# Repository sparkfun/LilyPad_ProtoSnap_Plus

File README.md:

SparkFun LilyPad ProtoSnap Plus
========================================

<table class="table table-hover table-striped table-bordered">
  <tr>
   <td><a href="https://www.sparkfun.com/products/14346"><div align="center"></div></a></center></td>
   <td><a href="https://www.sparkfun.com/products/12922"><div align="center"></div></a></td>
  </tr>
  <tr>
    <td><div align="center">LilyPad ProtoSnap Plus [<a href="https://www.sparkfun.com/products/14346">DEV-14346</a> ]</div></td>
    <td><div align="center">LilyPad ProtoSnap Plus Kit [<a href="https://www.sparkfun.com/products/12922">DEV-12922</a>]</div></td>
  </tr>
</table>

Snappable prototyping board with 32u4, light sensor, buzzer, button, and leds. 

To use the ProtoSnap Plus with Arduino, install the [SparkFun Arduino_Boards](https://github.com/sparkfun/Arduino_Boards) package for avr version 1.1.7 or later.

Base examples for this board are included in the package.  Select "LilyPad USB Plus" as a board type, then see examples for that board.

For extra information on Linux use, see [/Documentation/LinuxInstallation.md](https://github.com/sparkfun/LilyPad_ProtoSnap_Plus/tree/master/Documentation/LinuxInstallation.md).

Repository Contents
-------------------

* **/Documentation** - pin mapping and design information, linux installation info.
* **/Hardware** - Eagle design files (.brd, .sch)
* **/Production** - Production panel files (.brd)

Documentation
--------------
* **[Hookup Guide](https://learn.sparkfun.com/tutorials/lilypad-protosnap-plus-hookup-guide)** - Basic hookup guide for the LilyPad ProtoSnap Plus.
* **[Activity Guide](https://learn.sparkfun.com/tutorials/lilypad-protosnap-plus-activity-guide)** - This guide will get you started with some introductory programming activities exploring each of the LilyPad pieces on the LilyPad ProtoSnap Plus. If you’ve never used Arduino to program before, this guide will walk you through the basics with example code to upload and explore.

Product Versions
----------------
* [DEV-14346](https://www.sparkfun.com/products/14346) - LilyPad ProtoSnap Plus
* [DEV-12922](https://www.sparkfun.com/products/12922) - LilyPad ProtoSnap Plus Kit Version
* [LAB-14529](https://www.sparkfun.com/products/14529) - LilyPad ProtoSnap Plus Lab Pack Version

Version History
---------------
* [V_1.0](https://github.com/sparkfun/LilyPad_ProtoSnap_Plus/tree/V_0.1) - Production release.

License Information
-------------------

This product is _**open source**_! 

Please review the LICENSE.md file for license information. 

If you have any questions or concerns on licensing, please contact techsupport@sparkfun.com.

Distributed as-is; no warranty is given.

- Your friends at SparkFun.

_<COLLABORATION CREDIT>_

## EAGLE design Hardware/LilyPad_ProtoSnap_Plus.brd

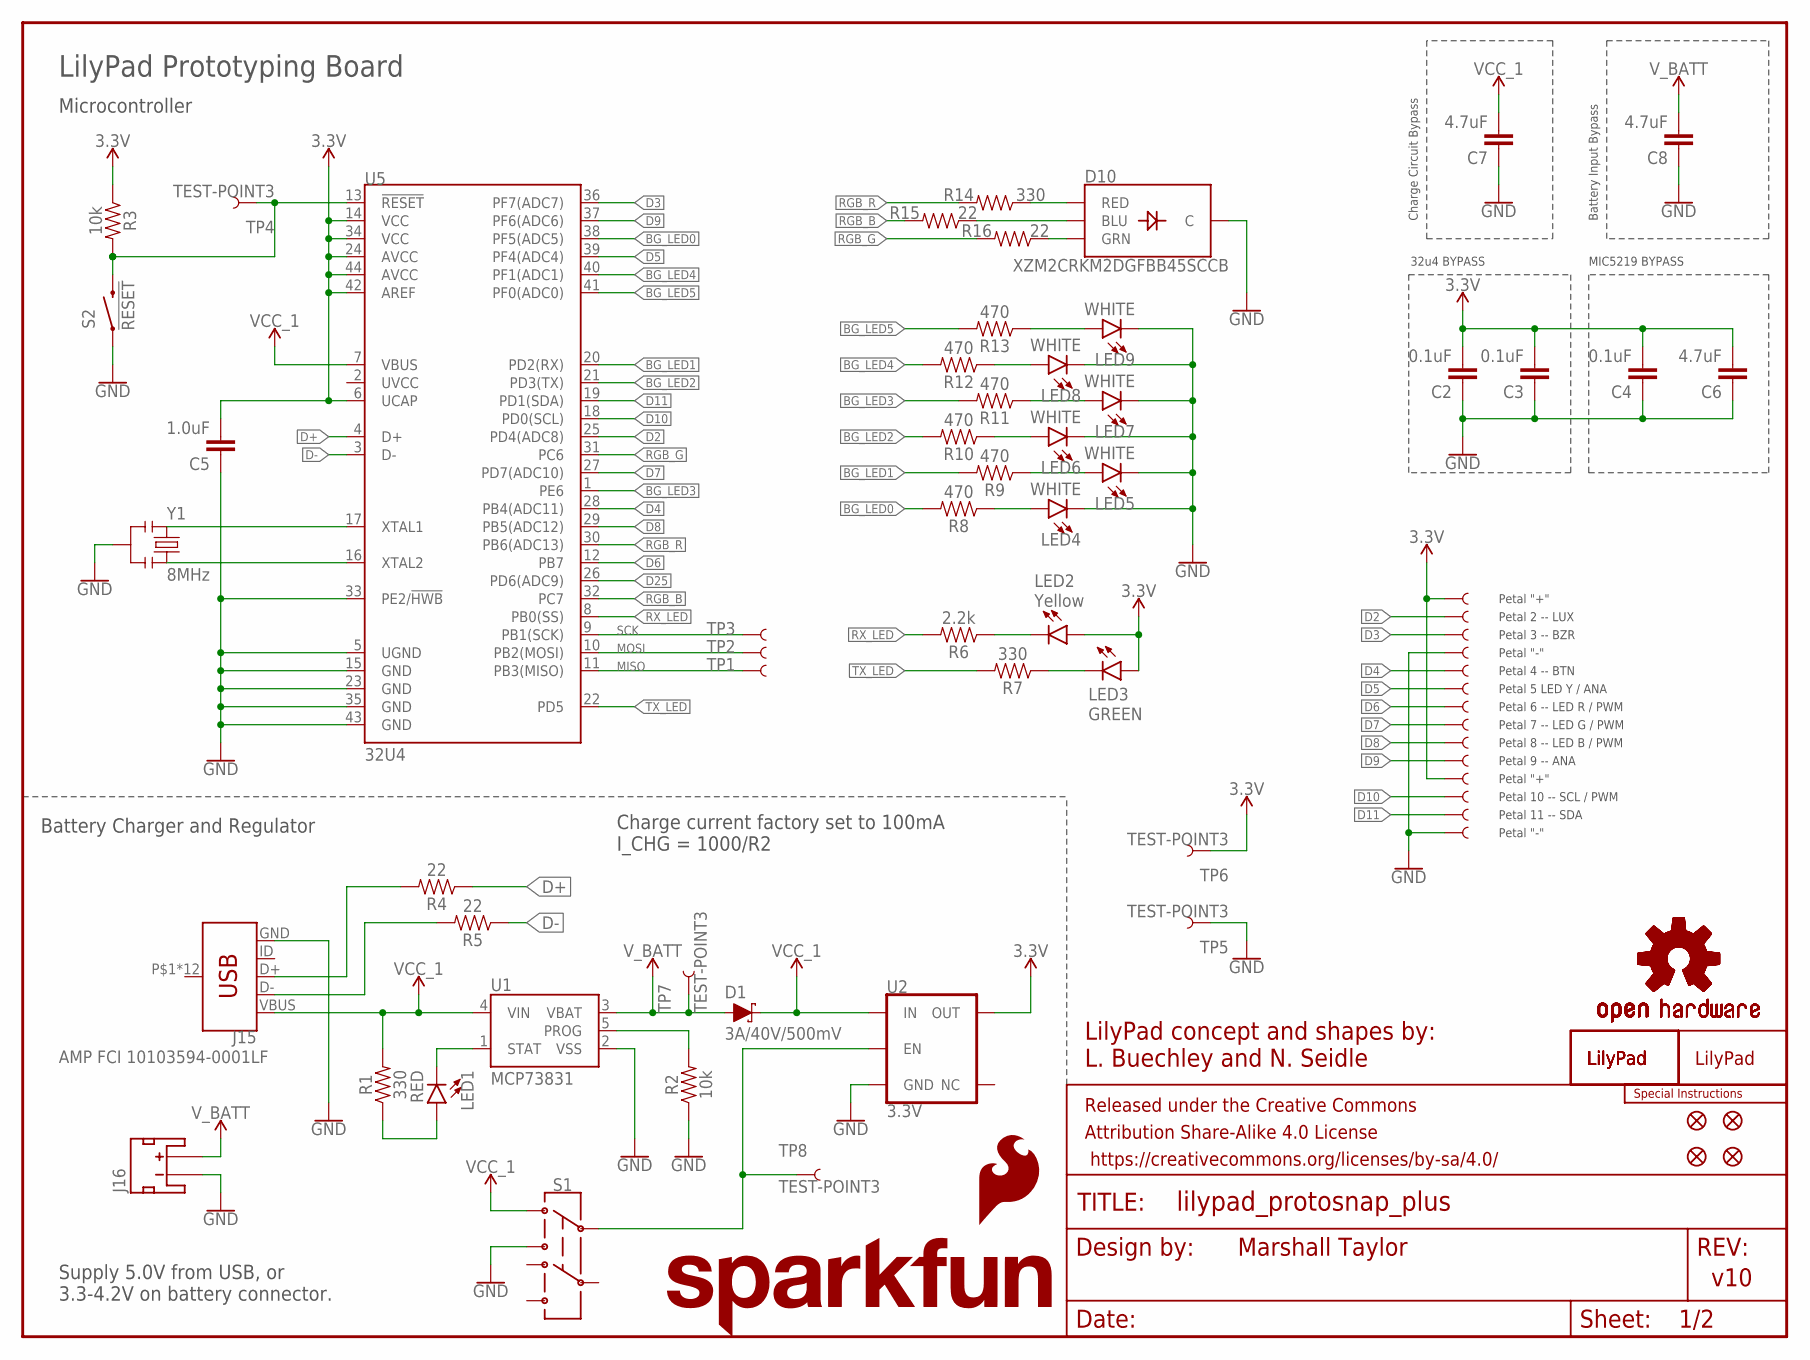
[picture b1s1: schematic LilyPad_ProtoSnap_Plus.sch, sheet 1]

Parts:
C2, C3, C4: 0.1uF; 0402
C5: 1.0uF; 0402
C6, C7, C8: 4.7uF; 0603
D1: 3A/40V/500mV; SMA-DIODE
D10: XZM2CRKM2DGFBB45SCCB; PLCC4SMDLED
FRAME1: FRAME-LETTER; CREATIVE_COMMONS
J1, J2, J3, J4, J5, J6, J7, J8, J9, J10, J11, J12, J13, J14: SEWTAP_LONG-2SIDE; PETAL-LONG-1-2SIDE
J15: AMP FCI 10103594-0001LF; USB-MICROB-PTH
J16: JST_2MM_MALE; JST-2-SMD
JP2, JP3, JP11, JP14: FIDUCIALUFIDUCIAL; MICRO-FIDUCIAL
LED1: RED; LED-0603
LED2: Yellow; LED-0603
LED3: GREEN; LED-0603
LED4, LED5, LED6, LED7, LED8, LED9: WHITE; LED-0603
LOGO1: SFE_LOGO_NAME.1_INCH; SFE_LOGO_NAME_.1
LOGO2: SFE_LOGO_FLAME.1EXP; SFE_LOGO_FLAME_COPPER_EXPOSED_.1
LOGO4, LOGO5, LOGO6: OSHW-LOGOS; OSHW-LOGO-S
R1, R7, R14: 330; 0603
R2, R3: 10k; 0603
R4, R5, R15, R16: 22; 0402
R6: 2.2k; 0603
R8, R9, R10, R11, R12, R13: 470; 0402
S1: SWITCH-DPDT-SMD-AYZ0202; SWITCH_DPDT_SMD_AYZ0202
S2: !RESET; TACTILE_SWITCH_SMD_5.2MM
TP1, TP2, TP3, TP4, TP5, TP6, TP7, TP8: TEST-POINT3; PAD.03X.03
U1: MCP73831; SOT23-5
U2: 3.3V; SOT23-5
U5: 32U4; QFN-44-PAD_1:1-LESS_PASTE
U$1, U$13, U$43: LILYLOGO_SHORT; LILYPAD-WEARABLES_LOGO-LILYPAD
U$44: SPECIAL_INSTRUCTIONS-ORDERING; ORDERING_INSTRUCTIONS
U$73: LILYLOGO_ABR; LILYPAD-WEARABLES_LOGO-L
Y1: 8MHz; RESONATOR-SMD

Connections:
3.3V: C2.2, C3.2, C4.2, C5.2, C6.2, J1.1, J11.1, LED2.A, LED3.A, R3.1, TP6.P$1, U2.5 (OUT), U5.6 (UCAP), U5.14 (VCC), U5.24 (AVCC), U5.34 (VCC), U5.42 (AREF), U5.44 (AVCC); also elsewhere on the board
BG_LED0: R8.2, U5.38 (PF5(ADC5))
BG_LED1: R9.2, U5.20 (PD2(RX))
BG_LED2: R10.2, U5.21 (PD3(TX))
BG_LED3: R11.2, U5.1 (PE6)
BG_LED4: R12.2, U5.40 (PF1(ADC1))
BG_LED5: R13.2, U5.41 (PF0(ADC0))
D2: J2.1, U5.25 (PD4(ADC8)); also elsewhere on the board
D3: J3.1, U5.36 (PF7(ADC7)); also elsewhere on the board
D4: J5.1, U5.28 (PB4(ADC11)); also elsewhere on the board
D5: J6.1, U5.39 (PF4(ADC4)); also elsewhere on the board
D6: J7.1, U5.12 (PB7); also elsewhere on the board
D7: J8.1, U5.27 (PD7(ADC10)); also elsewhere on the board
D8: J9.1, U5.29 (PB5(ADC12)); also elsewhere on the board
D9: J10.1, U5.37 (PF6(ADC6)); also elsewhere on the board
D10: J12.1, U5.18 (PD0(SCL)); also elsewhere on the board
D11: J13.1, U5.19 (PD1(SDA)); also elsewhere on the board
D25: U5.26 (PD6(ADC9))
D+: R4.1, U5.4 (D+)
D-: R5.1, U5.3 (D-)
GND: C2.1, C3.1, C4.1, C5.1, C6.1, C7.1, C8.1, D10.4 (C), J4.1, J14.1, J15.GND, J16.1 (-), LED4.C, LED5.C, LED6.C, LED7.C, LED8.C, LED9.C, R2.1, S1.3, S2.1, S2.2 (1), TP5.P$1, U1.2 (VSS), U2.2 (GND), U5.5 (UGND), U5.15 (GND), U5.23 (GND), U5.33 (PE2/!HWB), U5.35 (GND), U5.43 (GND), Y1.2; also elsewhere on the board
MISO: TP1.P$1, U5.11 (PB3(MISO))
MOSI: TP2.P$1, U5.10 (PB2(MOSI))
unnamed: LED2.C, R6.1
unnamed: S1.2, TP8.P$1, U2.3 (EN)
unnamed: LED1.A, R1.1
unnamed: LED1.C, U1.1 (STAT)
unnamed: U5.17 (XTAL1), Y1.1
unnamed: R2.2, U1.5 (PROG)
unnamed: U5.16 (XTAL2), Y1.3
unnamed: D10.2 (GRN), R16.1
unnamed: LED7.A, R11.1
unnamed: LED6.A, R10.1
unnamed: LED5.A, R9.1
unnamed: LED8.A, R12.1
unnamed: LED9.A, R13.1
unnamed: D10.3 (BLU), R15.1
unnamed: D10.1 (RED), R14.1
unnamed: LED4.A, R8.1
unnamed: J15.D-, R5.2
unnamed: J15.D+, R4.2
unnamed: LED3.C, R7.1
RESET: R3.2, S2.3 (2), S2.4 (2), TP4.P$1, U5.13 (!RESET)
RGB_B: R15.2, U5.32 (PC7)
RGB_G: R16.2, U5.31 (PC6)
RGB_R: R14.2, U5.30 (PB6(ADC13))
RX_LED: R6.2, U5.8 (PB0(SS))
SCK: TP3.P$1, U5.9 (PB1(SCK))
TX_LED: R7.2, U5.22 (PD5)
VCC_1: C7.2, D1.C, J15.VBUS, R1.2, S1.1, U1.4 (VIN), U2.1 (IN), U5.7 (VBUS)
V_BATT: C8.2, D1.A, J16.2 (+), TP7.P$1, U1.3 (VBAT)

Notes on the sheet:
32u4 BYPASS
MIC5219 BYPASS
Marshall Taylor
v10
LilyPad concept and shapes by: L. Buechley and N. Seidle
Charge Circuit Bypass
Battery Input Bypass
Petal 2 -- LUX
Petal 3 -- BZR
Petal 4 -- BTN
Petal 5 LED Y / ANA
Petal 6 -- LED R / PWM
Petal 7 -- LED G / PWM
Petal 8 -- LED B / PWM
Petal 9 -- ANA
Petal 10 -- SCL / PWM
Petal 11 -- SDA
Petal "+"
Petal "-"
LilyPad Prototyping Board
Microcontroller
Battery Charger and Regulator
Charge current factory set to 100mA I_CHG = 1000/R2
Supply 5.0V from USB, or 3.3-4.2V on battery connector.

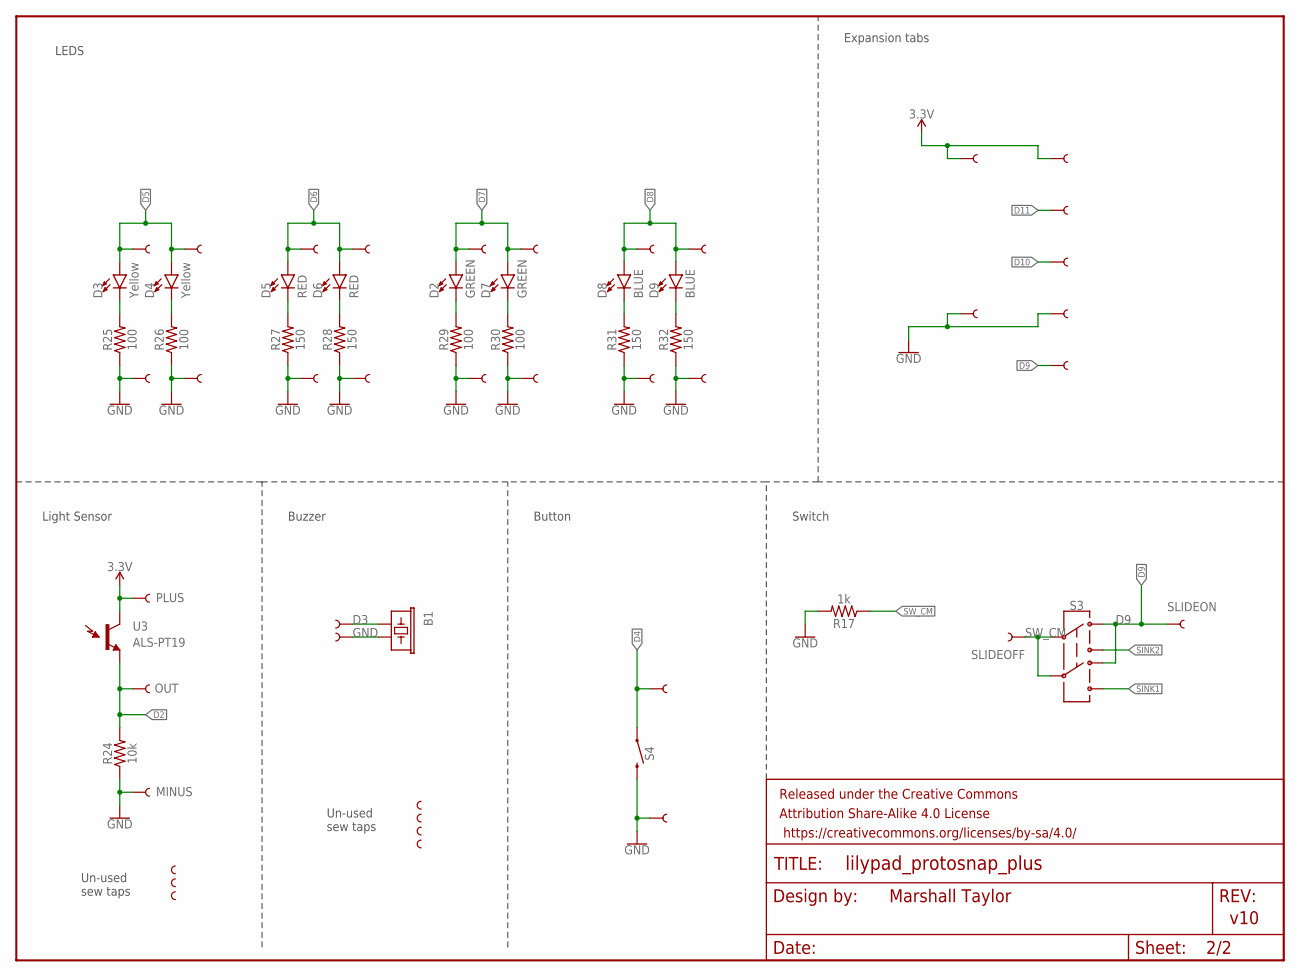
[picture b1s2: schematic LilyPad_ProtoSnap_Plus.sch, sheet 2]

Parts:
B1: Buzzer; BUZZER-CCV
D2, D7: GREEN; LED-1206
D3, D4: Yellow; LED-1206
D5, D6: RED; LED-1206
D8, D9: BLUE; LED-1206
FRAME2: FRAME-LETTERNO_PACKAGE; DUMMY
JP1, JP4, JP5, JP6, JP7, JP8, JP9, JP10, JP20, JP21, JP22, JP23, JP24, JP25, JP26, JP27: SEWTAP_SMALL-2SIDE; PETAL-SMALL-2SIDE
JP12, JP13: SEWTAP_MEDIUM-2SIDE; PETAL-MEDIUM-2SIDE
R17: 1k; 0603
R24: 10k; 0603
R25, R26, R29, R30: 100; 0603
R27, R28, R31, R32: 150; 0603
S3: SWITCH-DPDT-SMD-AYZ0202; SWITCH_DPDT_SMD_AYZ0202
S4: MOMENTARY-SWITCH-SPST-SMD-5.2-REDUNDANT; TACTILE_SWITCH_SMD_5.2MM
SEWTAPLS+: PLUS; PETAL-SMALL-2SIDE
SEWTAPLS-: MINUS; PETAL-SMALL-2SIDE
SEWTAPLSOUT: OUT; PETAL-SMALL-2SIDE
SLIDEOFF: SEWTAP_MEDIUM-2SIDE; PETAL-MEDIUM-2SIDE
SLIDEON: SEWTAP_MEDIUM-2SIDE; PETAL-MEDIUM-2SIDE
ST1, ST2, ST3: SEWTAP-NOHOLE_SM_NH; PETAL-SMALL-NOHOLE
U3: ALS-PT19
U$35, U$36, U$37, U$40: SEWTAP-NOHOLE_SM_NH; PETAL-SMALL-NOHOLE
U$38, U$39: SEWTAP_SMALL-2SIDE; PETAL-SMALL-2SIDE
U$41, U$42, U$51/SDA, U$52/SCL, U$52/SCL1, U$53, U$54: GATOR_HOLE_PAIR; GATOR_HOLES

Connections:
3.3V: SEWTAPLS+.1, U3.C (C1), U$41.P$1, U$41.P$2, U$42.P$1, U$42.P$2; also elsewhere on the board
D2: R24.2, SEWTAPLSOUT.1, U3.E (E1); also elsewhere on the board
D3: B1.+ (1), U$39.1; also elsewhere on the board
D4: JP12.1, S4.1, S4.2 (1); also elsewhere on the board
D5: D3.A, D4.A, JP20.1, JP22.1; also elsewhere on the board
D6: D5.A, D6.A, JP24.1, JP26.1; also elsewhere on the board
D7: D2.A, D7.A, JP7.1, JP8.1; also elsewhere on the board
D8: D8.A, D9.A, JP9.1, JP10.1; also elsewhere on the board
D9: S3.1, S3.4, SLIDEON.1, U$52/SCL1.P$1, U$52/SCL1.P$2; also elsewhere on the board
D10: U$52/SCL.P$1, U$52/SCL.P$2; also elsewhere on the board
D11: U$51/SDA.P$1, U$51/SDA.P$2; also elsewhere on the board
GND: B1.- (2), JP1.1, JP4.1, JP5.1, JP6.1, JP13.1, JP21.1, JP23.1, JP25.1, JP27.1, R17.2, R24.1, R25.1, R26.1, R27.1, R28.1, R29.1, R30.1, R31.1, R32.1, S4.3 (2), S4.4 (2), SEWTAPLS-.1, U$38.1, U$53.P$1, U$53.P$2, U$54.P$1, U$54.P$2; also elsewhere on the board
unnamed: D3.C, R25.2
unnamed: D4.C, R26.2
unnamed: D5.C, R27.2
unnamed: D6.C, R28.2
SINK1: S3.6
SINK2: S3.3
SW_CM: R17.1, S3.2, S3.5, SLIDEOFF.1
X003: D2.C, R29.2
X004: D7.C, R30.2
X005: D8.C, R31.2
X006: D9.C, R32.2

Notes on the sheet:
Un-used sew taps
Light Sensor
Button
LEDS
Expansion tabs
Buzzer
Marshall Taylor
v10
Switch

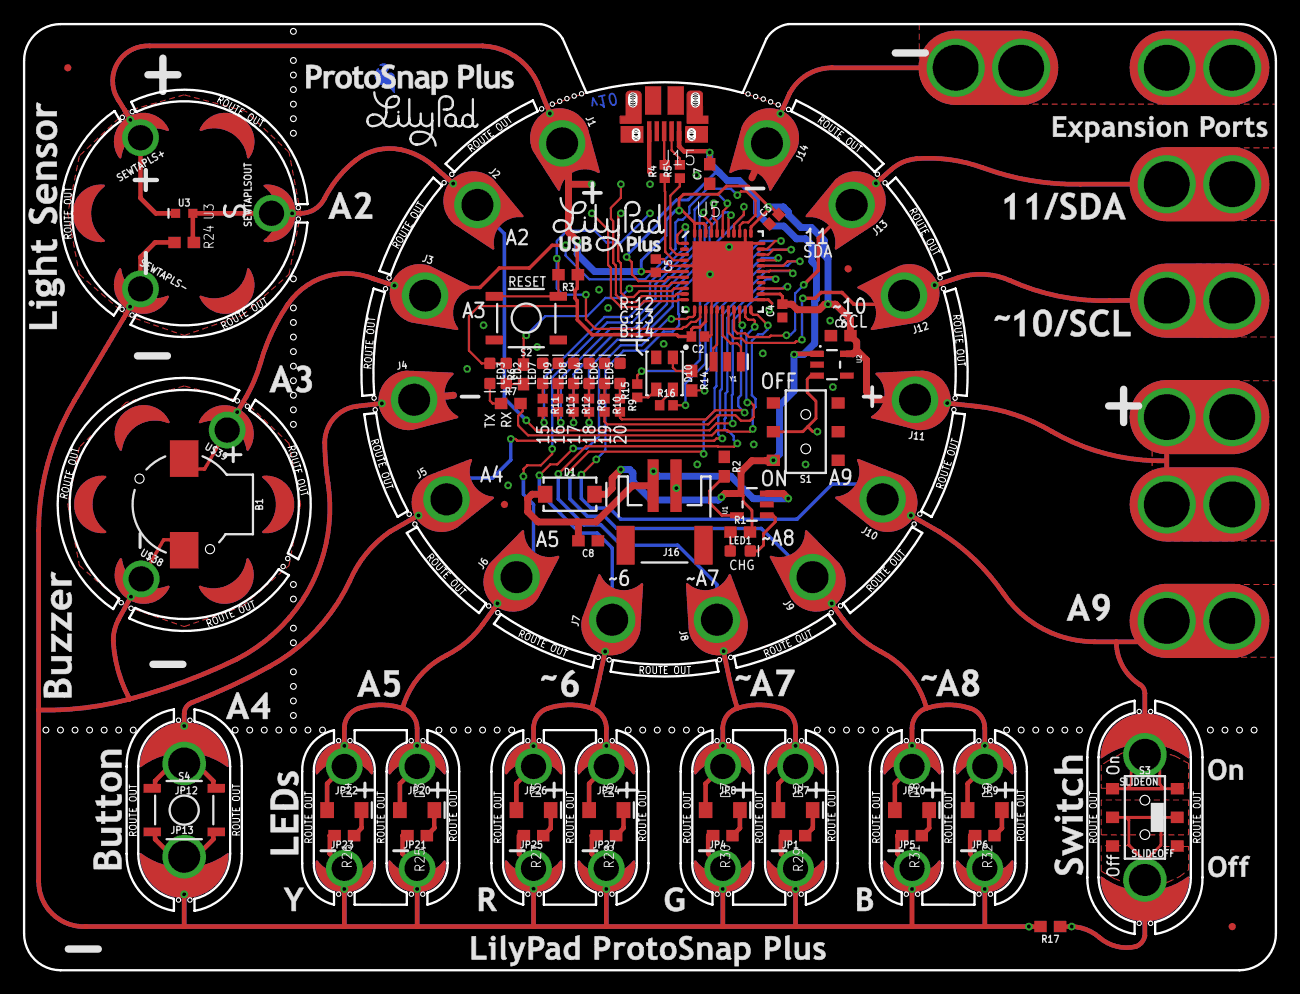
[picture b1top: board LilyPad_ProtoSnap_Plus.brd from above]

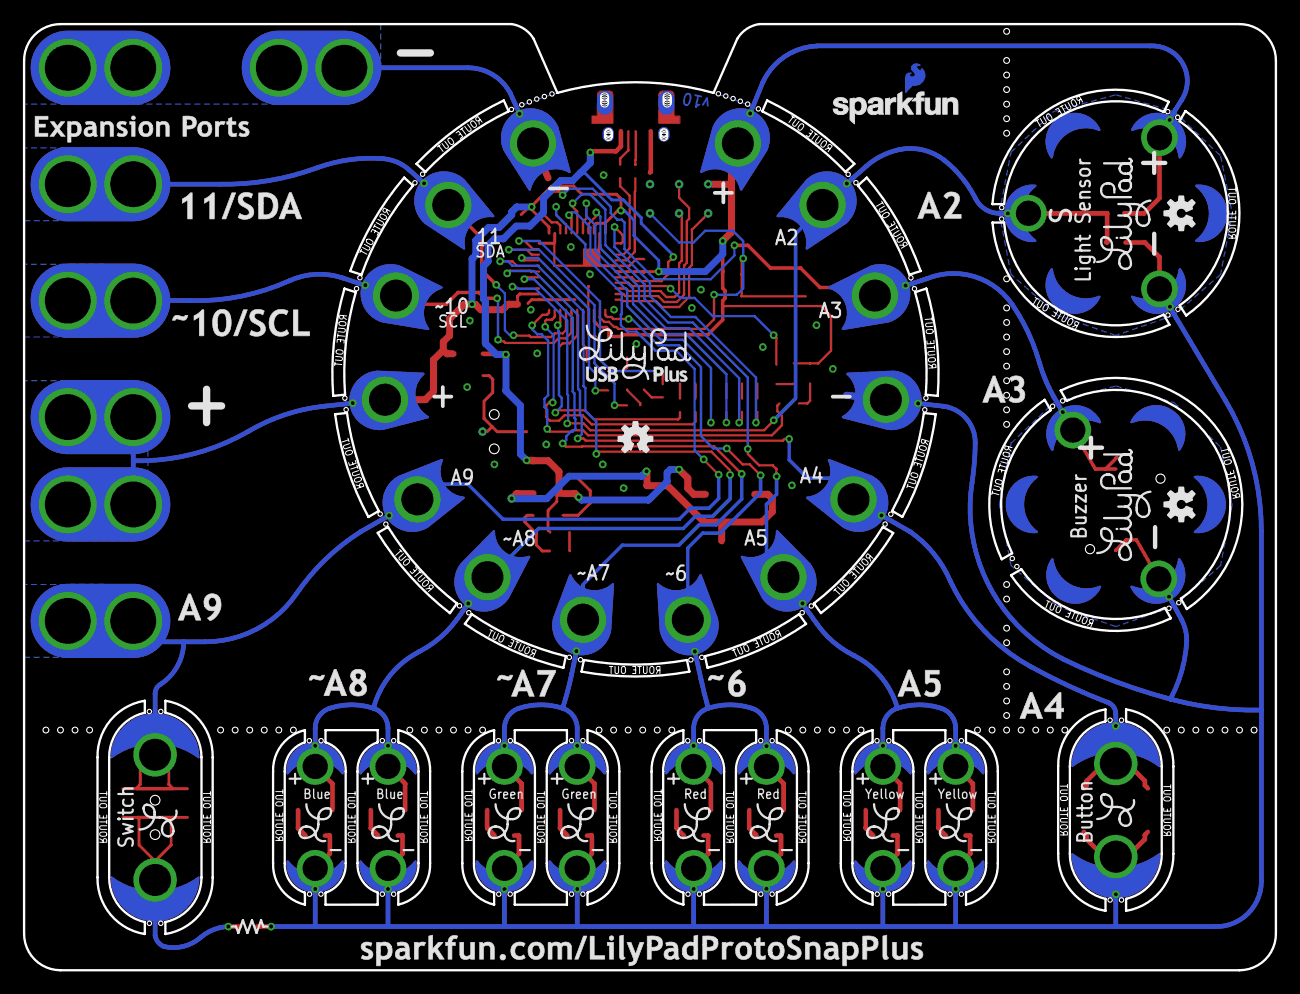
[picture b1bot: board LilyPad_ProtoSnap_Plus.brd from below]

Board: 2 copper layers, 109.2 x 82.5 mm, 197 parts (26 on the bottom side), 59 nets.

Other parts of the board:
L001, L002, L003, L004: LOGO-L
U$3, U$9, U$11, U$15, U$17, U$19, U$21, U$23, U$25, U$27, U$29, U$31, U$33, U$34: PETAL_PAD_OFF
U$5, U$6: LILYLOGO_SHORT; LILYPAD-WEARABLES_LOGO-LILYPAD
U$7, U$8, U$10, U$12, U$16, U$18, U$20, U$22, U$24, U$26, U$28, U$30, U$32: PETAL_SPACE_OFF
U$45, U$46, U$48, U$49, U$50: LOGO-L
U$51, U$52, U$55, U$56, U$57, U$58, U$59, U$60, U$61, U$62, U$63, U$64, U$65, U$66, U$67, U$68, U$70, U$71: ROUTE_TICKS

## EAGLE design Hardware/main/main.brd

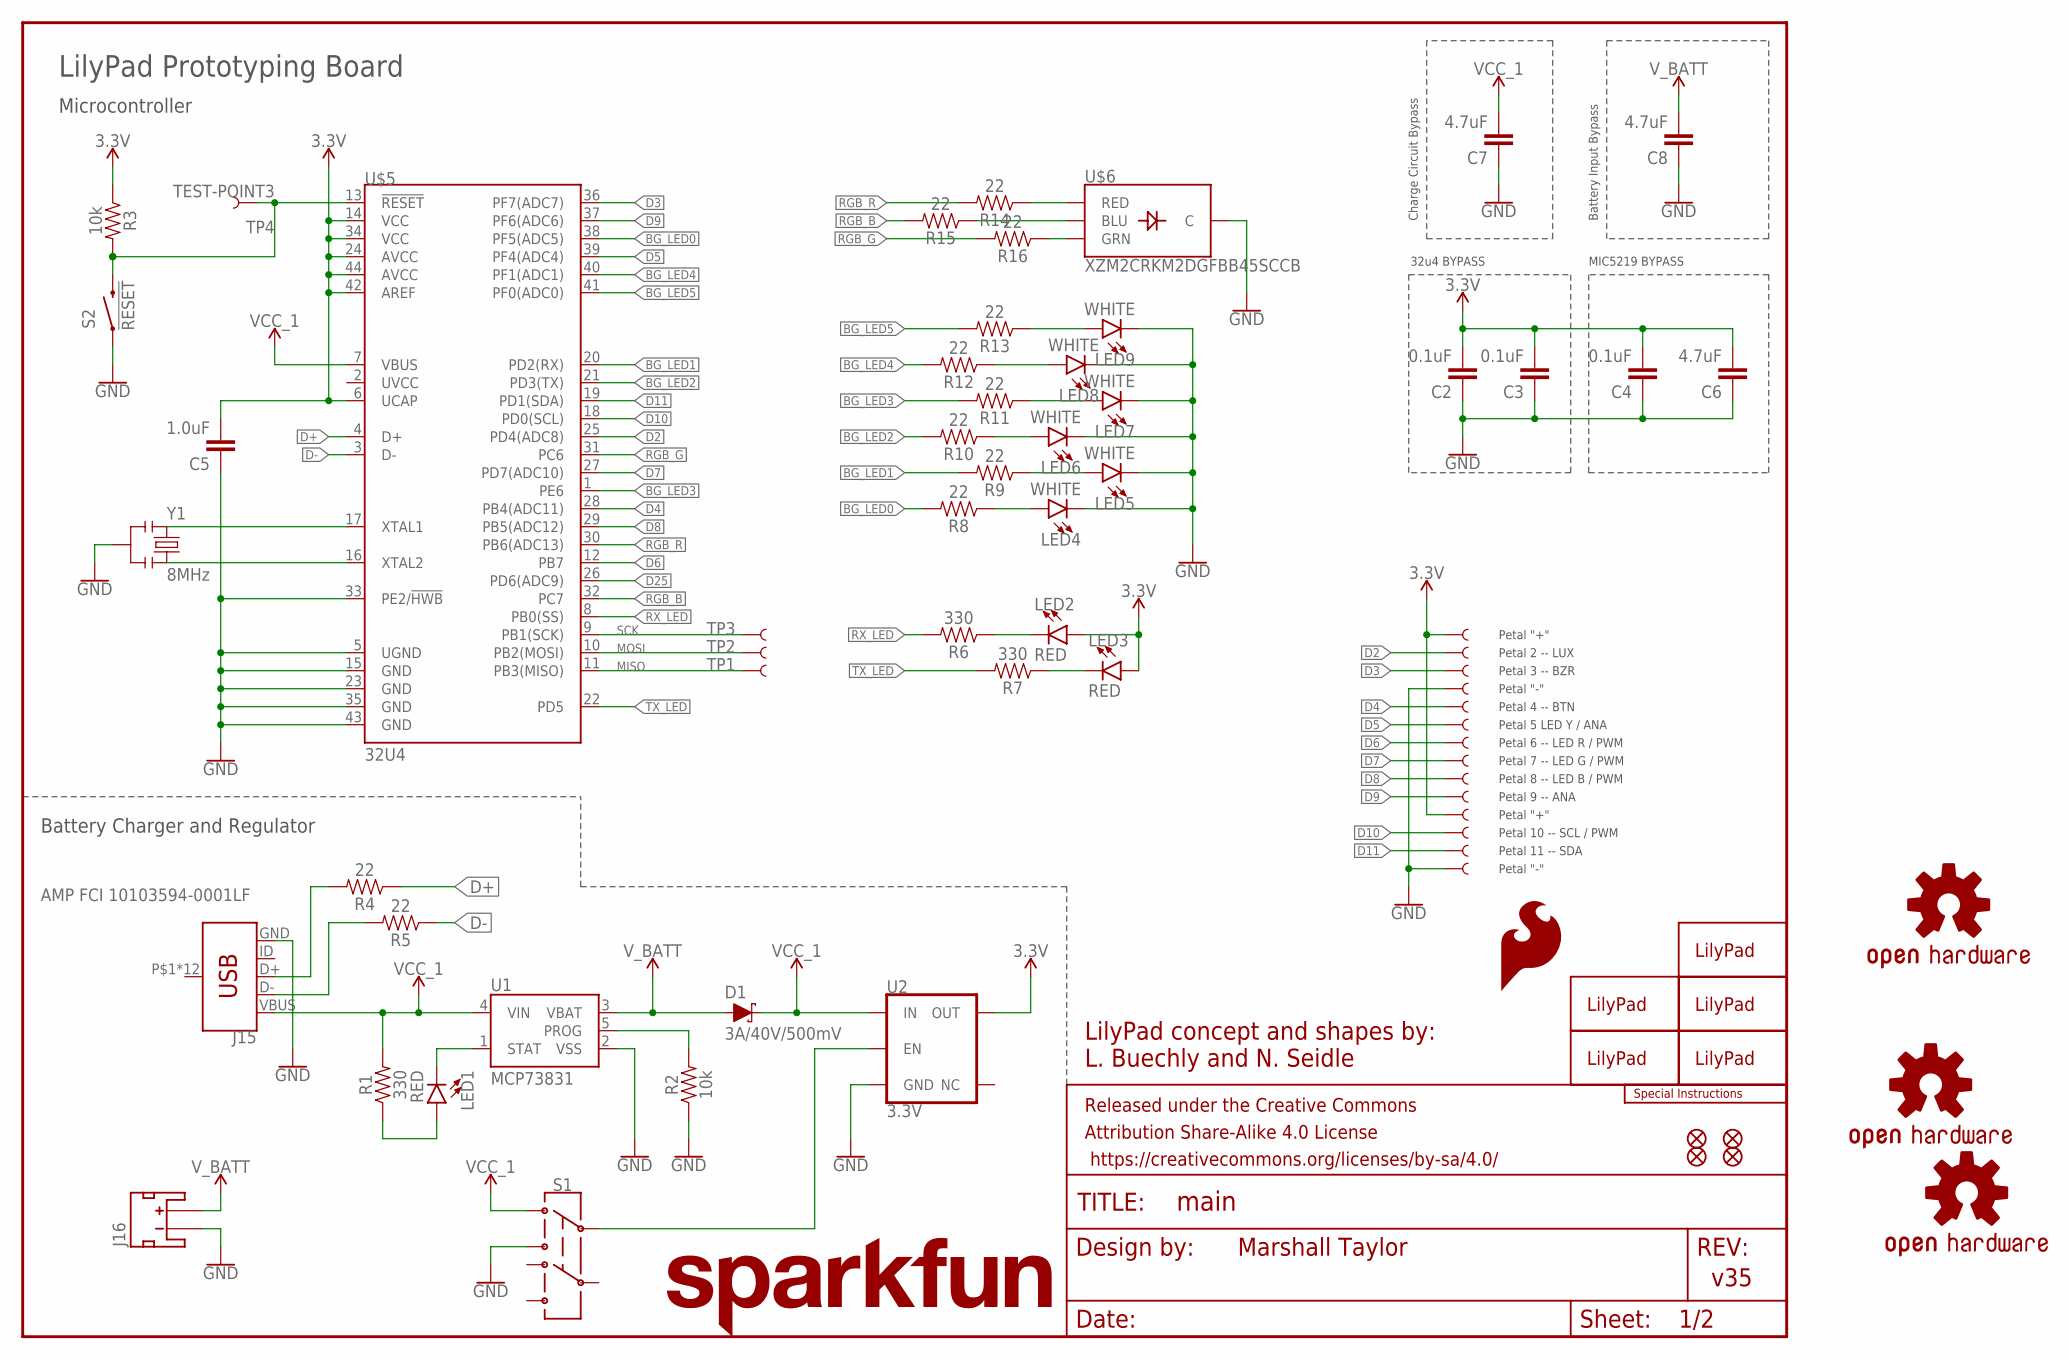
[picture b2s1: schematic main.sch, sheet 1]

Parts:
C2, C3, C4: 0.1uF; 0402
C5: 1.0uF; 0402
C6, C7, C8: 4.7uF; 0603
D1: 3A/40V/500mV; SMA-DIODE
FRAME1: FRAME-LETTER; CREATIVE_COMMONS
J1, J2, J3, J4, J5, J6, J7, J8, J9, J10, J11, J12, J13, J14: SEWTAP_LONG; PETAL-LONG-1
J15: AMP FCI 10103594-0001LF; USB-MICROB-PTH
J16: JST_2MM_MALE; JST-2-SMD
JP2, JP3, JP11, JP14: FIDUCIALUFIDUCIAL; MICRO-FIDUCIAL
LED1, LED2, LED3: RED; LED-0603
LED4, LED5, LED6, LED7, LED8, LED9: WHITE; LED-0603
LOGO1: SFE_LOGO_NAME.1_INCH; SFE_LOGO_NAME_.1
LOGO2: SFE_LOGO_FLAME.1EXP; SFE_LOGO_FLAME_COPPER_EXPOSED_.1
LOGO4, LOGO5, LOGO6: OSHW-LOGOS; OSHW-LOGO-S
R1, R6, R7: 330; 0603
R2, R3: 10k; 0603
R4, R5, R8, R9, R10, R11, R12, R13, R14, R15, R16: 22; 0402
S1: SWITCH-DPDT-SMD-AYZ0202; SWITCH_DPDT_SMD_AYZ0202
S2: !RESET; TACTILE_SWITCH_SMD_5.2MM
TP1, TP2, TP3, TP4: TEST-POINT3; PAD.03X.03
U1: MCP73831; SOT23-5
U2: 3.3V; SOT23-5
U$1, U$13: LILYLOGO_SHORT; LILYPAD-WEARABLES_LOGO-LILYPAD
U$5: 32U4; QFN-44
U$6: XZM2CRKM2DGFBB45SCCB; PLCC4SMDLED
U$43, U$72, U$73: LILYLOGO_ABR; LILYPAD-WEARABLES_LOGO-L
U$44: SPECIAL_INSTRUCTIONS-ORDERING; ORDERING_INSTRUCTIONS
Y1: 8MHz; RESONATOR-SMD

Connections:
3.3V: C2.2, C3.2, C4.2, C5.2, C6.2, J1.1, J11.1, LED2.A, LED3.A, R3.1, U2.5 (OUT), U$5.6 (UCAP), U$5.14 (VCC), U$5.24 (AVCC), U$5.34 (VCC), U$5.42 (AREF), U$5.44 (AVCC); also elsewhere on the board
BG_LED0: R8.2, U$5.38 (PF5(ADC5))
BG_LED1: R9.2, U$5.20 (PD2(RX))
BG_LED2: R10.2, U$5.21 (PD3(TX))
BG_LED3: R11.2, U$5.1 (PE6)
BG_LED4: R12.2, U$5.40 (PF1(ADC1))
BG_LED5: R13.2, U$5.41 (PF0(ADC0))
D2: J2.1, U$5.25 (PD4(ADC8)); also elsewhere on the board
D3: J3.1, U$5.36 (PF7(ADC7)); also elsewhere on the board
D4: J5.1, U$5.28 (PB4(ADC11)); also elsewhere on the board
D5: J6.1, U$5.39 (PF4(ADC4)); also elsewhere on the board
D6: J7.1, U$5.12 (PB7); also elsewhere on the board
D7: J8.1, U$5.27 (PD7(ADC10)); also elsewhere on the board
D8: J9.1, U$5.29 (PB5(ADC12)); also elsewhere on the board
D9: J10.1, U$5.37 (PF6(ADC6)); also elsewhere on the board
D10: J12.1, U$5.18 (PD0(SCL)); also elsewhere on the board
D11: J13.1, U$5.19 (PD1(SDA)); also elsewhere on the board
D25: U$5.26 (PD6(ADC9))
D+: R4.1, U$5.4 (D+)
D-: R5.1, U$5.3 (D-)
GND: C2.1, C3.1, C4.1, C5.1, C6.1, C7.1, C8.1, J4.1, J14.1, J15.GND, J16.1 (-), LED4.C, LED5.C, LED6.C, LED7.C, LED8.C, LED9.C, R2.1, S1.3, S2.1, S2.2 (1), U1.2 (VSS), U2.2 (GND), U$5.5 (UGND), U$5.15 (GND), U$5.23 (GND), U$5.33 (PE2/!HWB), U$5.35 (GND), U$5.43 (GND), U$6.4 (C), Y1.2; also elsewhere on the board
MISO: TP1.P$1, U$5.11 (PB3(MISO))
MOSI: TP2.P$1, U$5.10 (PB2(MOSI))
unnamed: LED2.C, R6.1
unnamed: S1.2, U2.3 (EN)
unnamed: LED1.A, R1.1
unnamed: LED1.C, U1.1 (STAT)
unnamed: U$5.17 (XTAL1), Y1.1
unnamed: R2.2, U1.5 (PROG)
unnamed: U$5.16 (XTAL2), Y1.3
unnamed: R16.1, U$6.2 (GRN)
unnamed: LED7.A, R11.1
unnamed: LED6.A, R10.1
unnamed: LED5.A, R9.1
unnamed: LED8.A, R12.1
unnamed: LED9.A, R13.1
unnamed: R15.1, U$6.3 (BLU)
unnamed: R14.1, U$6.1 (RED)
unnamed: LED4.A, R8.1
unnamed: J15.D-, R5.2
unnamed: J15.D+, R4.2
unnamed: LED3.C, R7.1
RESET: R3.2, S2.3 (2), S2.4 (2), TP4.P$1, U$5.13 (!RESET)
RGB_B: R15.2, U$5.32 (PC7)
RGB_G: R16.2, U$5.31 (PC6)
RGB_R: R14.2, U$5.30 (PB6(ADC13))
RX_LED: R6.2, U$5.8 (PB0(SS))
SCK: TP3.P$1, U$5.9 (PB1(SCK))
TX_LED: R7.2, U$5.22 (PD5)
VCC_1: C7.2, D1.C, J15.VBUS, R1.2, S1.1, U1.4 (VIN), U2.1 (IN), U$5.7 (VBUS)
V_BATT: C8.2, D1.A, J16.2 (+), U1.3 (VBAT)

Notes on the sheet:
32u4 BYPASS
MIC5219 BYPASS
Marshall Taylor
v35
LilyPad concept and shapes by: L. Buechly and N. Seidle
Charge Circuit Bypass
Battery Input Bypass
Petal 2 -- LUX
Petal 3 -- BZR
Petal 4 -- BTN
Petal 5 LED Y / ANA
Petal 6 -- LED R / PWM
Petal 7 -- LED G / PWM
Petal 8 -- LED B / PWM
Petal 9 -- ANA
Petal 10 -- SCL / PWM
Petal 11 -- SDA
Petal "+"
Petal "-"
LilyPad Prototyping Board
Microcontroller
Battery Charger and Regulator

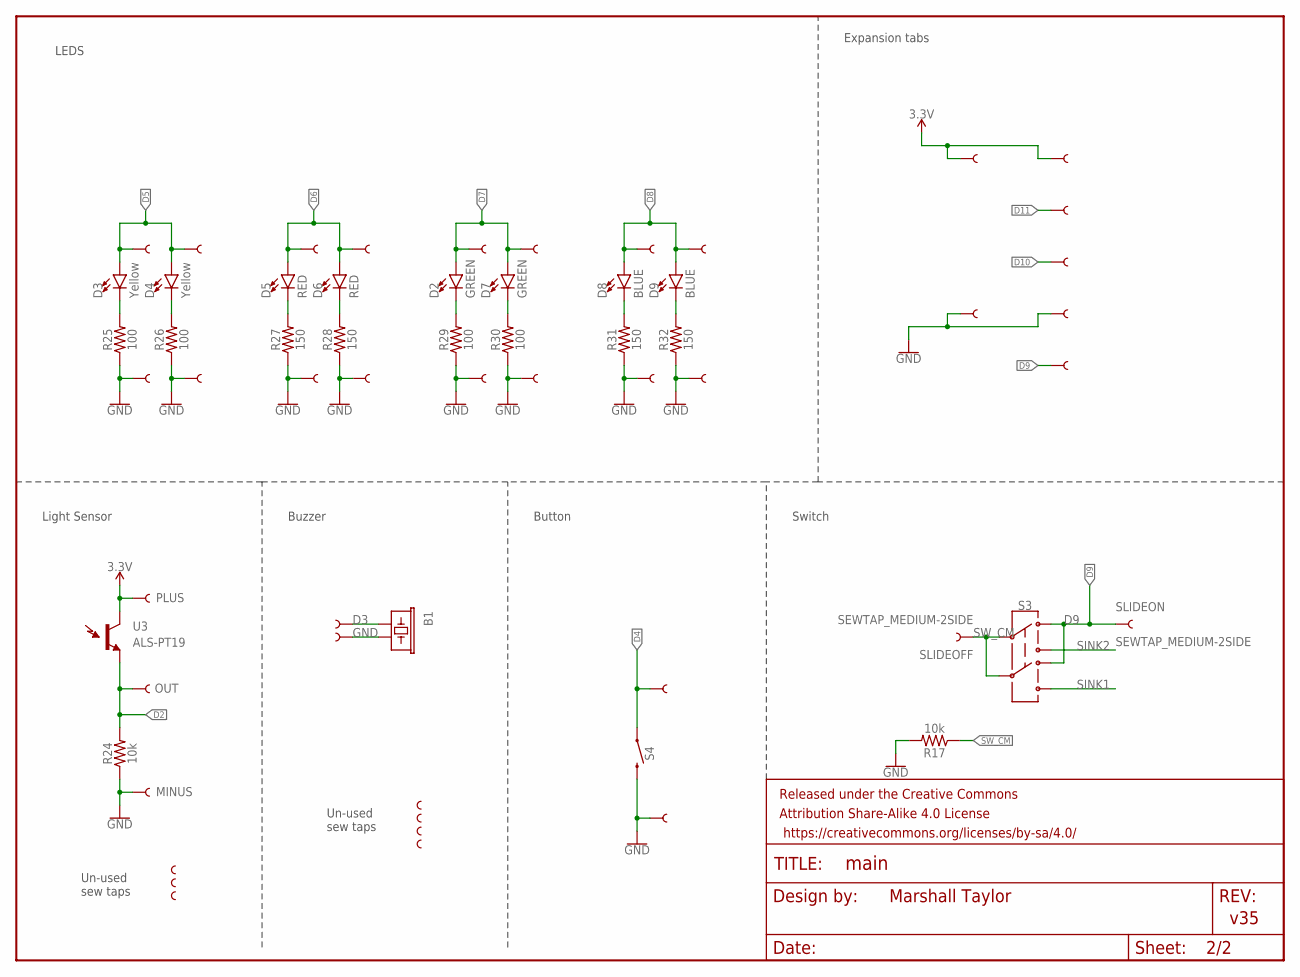
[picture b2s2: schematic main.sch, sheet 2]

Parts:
B1: Buzzer; BUZZER-CCV
D2, D7: GREEN; LED-1206
D3, D4: Yellow; LED-1206
D5, D6: RED; LED-1206
D8, D9: BLUE; LED-1206
FRAME2: FRAME-LETTERNO_PACKAGE; DUMMY
JP1, JP4, JP5, JP6, JP7, JP8, JP9, JP10, JP20, JP21, JP22, JP23, JP24, JP25, JP26, JP27: SEWTAP_SMALL-2SIDE; PETAL-SMALL-2SIDE
JP12, JP13: SEWTAP_MEDIUM-2SIDE; PETAL-MEDIUM-2SIDE
R17, R24: 10k; 0603
R25, R26, R29, R30: 100; 0603
R27, R28, R31, R32: 150; 0603
S3: SWITCH-DPDT-SMD-AYZ0202; SWITCH_DPDT_SMD_AYZ0202
S4: MOMENTARY-SWITCH-SPST-SMD-4.6X2.8MM; TACTILE_SWITCH_SMD_4.6X2.8MM
SEWTAPLS+: PLUS; PETAL-SMALL-2SIDE
SEWTAPLS-: MINUS; PETAL-SMALL-2SIDE
SEWTAPLSOUT: OUT; PETAL-SMALL-2SIDE
SLIDEOFF: SEWTAP_MEDIUM-2SIDE; PETAL-MEDIUM-2SIDE
SLIDEON: SEWTAP_MEDIUM-2SIDE; PETAL-MEDIUM-2SIDE
ST1, ST2, ST3: SEWTAP-NOHOLE_SM_NH; PETAL-SMALL-NOHOLE
U3: ALS-PT19
U$35, U$36, U$37, U$40: SEWTAP-NOHOLE_SM_NH; PETAL-SMALL-NOHOLE
U$38, U$39: SEWTAP_SMALL; PETAL-SMALL
U$41, U$42, U$51/SDA, U$52/SCL, U$52/SCL1, U$53, U$54: GATOR_HOLE_PAIR; GATOR_HOLES

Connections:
3.3V: SEWTAPLS+.1, U3.C (C1), U$41.P$1, U$41.P$2, U$42.P$1, U$42.P$2; also elsewhere on the board
D2: R24.2, SEWTAPLSOUT.1, U3.E (E1); also elsewhere on the board
D3: B1.+ (1), U$39.1; also elsewhere on the board
D4: JP12.1, S4.1, S4.2 (1); also elsewhere on the board
D5: D3.A, D4.A, JP20.1, JP22.1; also elsewhere on the board
D6: D5.A, D6.A, JP24.1, JP26.1; also elsewhere on the board
D7: D2.A, D7.A, JP7.1, JP8.1; also elsewhere on the board
D8: D8.A, D9.A, JP9.1, JP10.1; also elsewhere on the board
D9: S3.1, S3.4, SLIDEON.1, U$52/SCL1.P$1, U$52/SCL1.P$2; also elsewhere on the board
D10: U$52/SCL.P$1, U$52/SCL.P$2; also elsewhere on the board
D11: U$51/SDA.P$1, U$51/SDA.P$2; also elsewhere on the board
GND: B1.- (2), JP1.1, JP4.1, JP5.1, JP6.1, JP13.1, JP21.1, JP23.1, JP25.1, JP27.1, R17.2, R24.1, R25.1, R26.1, R27.1, R28.1, R29.1, R30.1, R31.1, R32.1, S4.3 (2), S4.4 (2), SEWTAPLS-.1, U$38.1, U$53.P$1, U$53.P$2, U$54.P$1, U$54.P$2; also elsewhere on the board
unnamed: D3.C, R25.2
unnamed: D4.C, R26.2
unnamed: D5.C, R27.2
unnamed: D6.C, R28.2
SINK1: S3.6
SINK2: S3.3
SW_CM: R17.1, S3.2, S3.5, SLIDEOFF.1
X003: D2.C, R29.2
X004: D7.C, R30.2
X005: D8.C, R31.2
X006: D9.C, R32.2

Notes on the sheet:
Un-used sew taps
Light Sensor
Button
LEDS
Expansion tabs
Buzzer
Marshall Taylor
v35
Switch

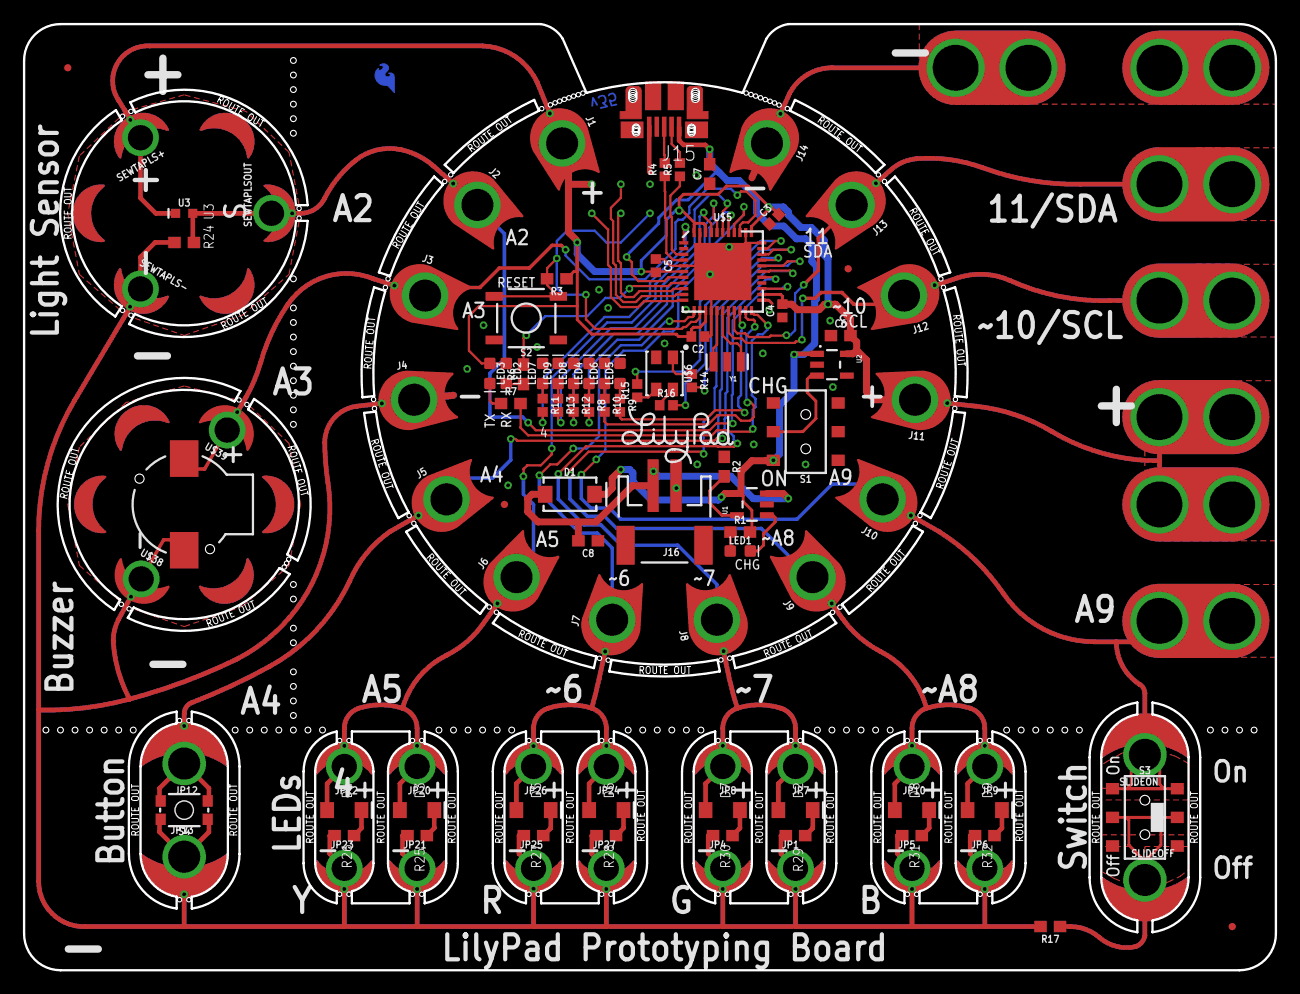
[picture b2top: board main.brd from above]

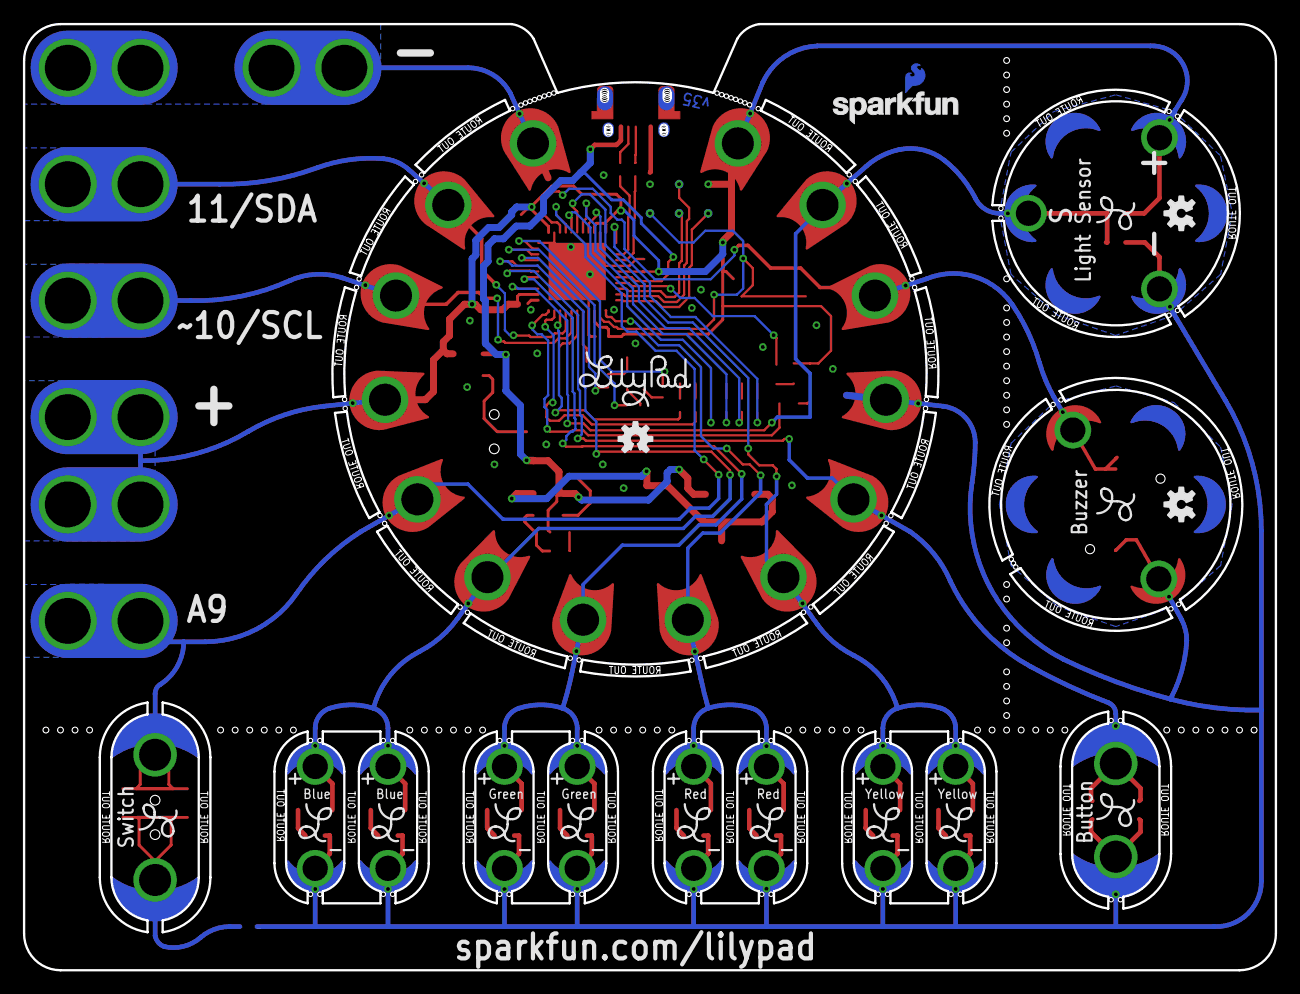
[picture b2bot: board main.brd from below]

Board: 2 copper layers, 109.2 x 82.5 mm, 193 parts (22 on the bottom side), 59 nets.

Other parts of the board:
L001, L002, L003, L004: LOGO-L
U$3, U$9, U$11, U$15, U$17, U$19, U$21, U$23, U$25, U$27, U$29, U$31, U$33, U$34: PETAL_PAD_OFF
U$7, U$8, U$10, U$12, U$16, U$18, U$20, U$22, U$24, U$26, U$28, U$30, U$32: PETAL_SPACE_OFF
U$45, U$46, U$48, U$49, U$50: LOGO-L
U$51, U$52, U$55, U$56, U$57, U$58, U$59, U$60, U$61, U$62, U$63, U$64, U$65, U$66, U$67, U$68, U$69, U$70, U$71: ROUTE_TICKS

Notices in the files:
parts and their libraries:
SparkFun-PowerIC: Licensing: CC v3.0 Share-Alike You are welcome to use this library for commercial purposes.
SparkFun-Aesthetics: Released under the Creative Commons Attribution Share-Alike 4.0 License
SparkFun-Aesthetics: Released under the Creative Commons
